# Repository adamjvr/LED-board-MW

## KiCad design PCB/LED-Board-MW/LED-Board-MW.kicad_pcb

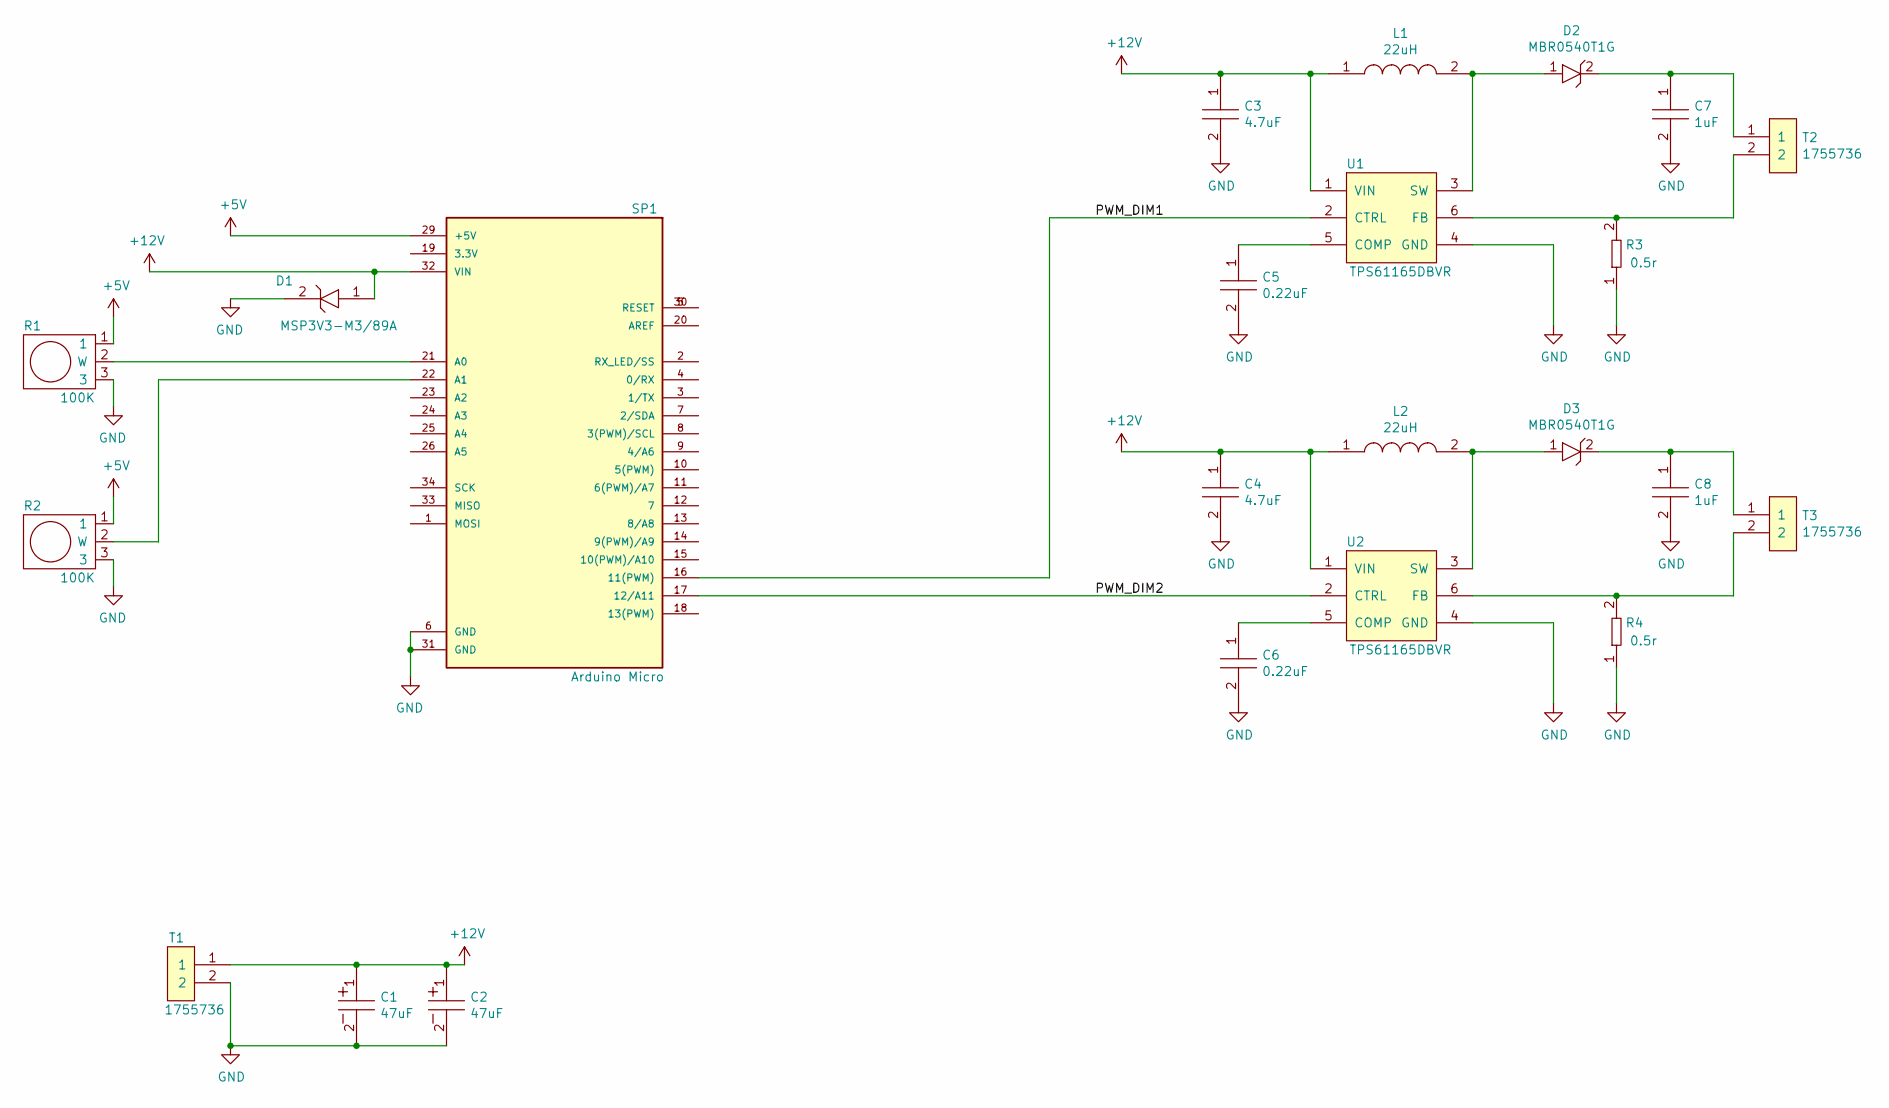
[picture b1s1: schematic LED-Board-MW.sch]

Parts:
C1, C2: UFW1H470MED1TD; CP_Radial_D6.3mm_P2.50mm; Tolerance 20%; Voltage 50V; MFR# UFW1H470MED1TD
C3, C4: CL21A475KACLRNC; C0805; Tolerance 10%; Voltage *; MFR# CL21A475KACLRNC
C5, C6: CL21B224KBFNNNE; C0805; Tolerance 10%; Voltage 50V; MFR# CL21B224KBFNNNE
C7, C8: C1206C105K3RACAUTO; D_SOD-123; Tolerance 10%; Voltage 25V; MFR# C1206C105K3RACAUTO
D1: MSP3V3-M3_89A; MSP3V3; Tolerance *; Voltage 3.3V; MFR# MSP3V3-M3/89A
D2, D3: MBR0540T1G; D_SOD-123; Tolerance *; Voltage 40V; MFR# MBR0540T1G
L1, L2: SRN8040-220M; Tolerance 20%; Voltage *; MFR# SRN8040-220M
R1, R2: P0915N-EC15BR100K; P0915N-FC15BR10K; Tolerance 20%; Voltage *; MFR# P0915N-EC15BR100K
R3, R4: WSLT2512R5000FEA; R2512; Tolerance 1%; Voltage *; MFR# WSLT2512R5000FEA
SP1: Arduino_Micro; ARDUINO_A000053; Tolerance *; Voltage 3.3V/5V; MFR# A000053
T1, T2, T3: 1755736; PhoenixContact_MSTBVA-G_02x5.08mm_Vertical; Tolerance *; Voltage 300V; MFR# 1755736
U1, U2: TPS61165DBVR; SOT-23-6_Handsoldering; Tolerance *; Voltage 3-18V IN 18-38V OUT; MFR# TPS61165DBVR

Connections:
+5V: R1.1, R2.1, SP1.29 (+5V)
+12V: C1.1, C2.1, C3.1, C4.1, D1.1, L1.1, L2.1, SP1.32 (VIN), T1.1, U1.1 (VIN), U2.1 (VIN)
/PWM_DIM1: SP1.16 (11(PWM)), U1.2 (CTRL)
/PWM_DIM2: SP1.17 (12/A11), U2.2 (CTRL)
GND: C1.2, C2.2, C3.2, C4.2, C5.2, C6.2, C7.2, C8.2, D1.2, R1.3, R2.3, R3.1, R4.1, SP1.6 (GND), SP1.31 (GND), T1.2, U1.4 (GND), U2.4 (GND)
unnamed: C5.1, U1.5 (COMP)
unnamed: C6.1, U2.5 (COMP)
unnamed: C7.1, D2.2, T2.1
unnamed: C8.1, D3.2, T3.1
unnamed: D2.1, L1.2, U1.3 (SW)
unnamed: D3.1, L2.2, U2.3 (SW)
unnamed: R1.2 (W), SP1.21 (A0)
unnamed: R2.2 (W), SP1.22 (A1)
unnamed: R3.2, T2.2, U1.6 (FB)
unnamed: R4.2, T3.2, U2.6 (FB)
unnamed: SP1.5 (RESET), SP1.30 (RESET)

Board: 2 copper layers, 23 parts (0 on the bottom side), 16 nets, no tracks yet.

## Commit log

2020-08-01 Schematic First Pass
    Finished first pass of schematic
2020-08-18 Board Started
    Started doing board based on schetaic, design make change since LEDs are huge

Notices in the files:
parts and their libraries:
Copyright 2016 Accelerated Designs. All rights reserved.
